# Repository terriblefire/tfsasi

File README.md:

# TFSASI - SASI to SCSI Adapter

A 3-way universal adapter board for connecting SASI 20-pin, SASI 26-pin, or SCSI 50-pin devices.

> **ℹ️ Tested:** SASI 20-pin (J1) with an X68000 EXPERT and a BlueSCSI.
>
> **⚠️ WARNING:** The SASI 26-pin connector (J2) has not yet been tested. Use at your own risk.

## Overview

This adapter allows you to connect:
- SASI 20-pin devices to SCSI 50-pin controllers
- SASI 26-pin devices to SCSI 50-pin controllers
- Mix and match between different SASI and SCSI interfaces

## Features

- **3-way adapter**: SASI 20-pin, SASI 26-pin, and SCSI 50-pin connectors
- **4-layer PCB design** for improved signal integrity
- **All signals properly mapped** between connectors
- **LED header connections provided** - Separate headers are included for HDD activity LED signals (SASI-20 pin 12, SASI-26 pin 16) to allow for custom LED driver circuits
- **Mirrored connector footprints** for proper cable orientation
- **Full SCSI-1 compatibility** with parity and attention signals (on 26-pin)

## Connectors

### SASI 20-Pin (J1)
- 2x10 pin header (0.1" pitch)
- Basic SASI interface with data and control signals
- No parity or attention signals
- Pin 12 (LED) is not connected

### SASI 26-Pin (J2)
- 2x13 pin header (0.1" pitch)
- Full SCSI-compatible with parity and attention
- Includes TERMPWR (+5V for termination)
- Pin 16 (LED) is not connected

### SCSI 50-Pin (J3)
- 2x25 pin header (0.1" pitch)
- Standard SCSI-1 interface
- Pin 18 (DBP/parity) connects from SASI 26-pin
- Pin 32 (ATN) connects from SASI 26-pin only

## Assembly

All three connector footprints are **mirrored** (a mirror image of a standard header when viewed from the top). The connectors must therefore be fitted on specific sides of the board, or the signals will be scrambled (odd/even rows swapped):

| Connector | Part | Fit on | Mates with |
|-----------|------|--------|------------|
| J1 (SASI 20-pin) | Male pin header | **Bottom** side (pins pointing down) | Ribbon cable, plugged in from below |
| J2 (SASI 26-pin) | Male pin header | **Bottom** side (pins pointing down) | Ribbon cable, plugged in from below |
| J3 (SCSI 50-pin) | Female pin socket | **Top** side | Male 50-pin header of the SCSI device (e.g. BlueSCSI), mounted face-to-face from above |

- Orient each ribbon cable so the stripe (pin 1) is at the square pad end.
- Leave JP1/JP2 open unless you need the LED signal; SCSI pin 34 is GND on most SCSI devices.
- **Verify after assembly:** with everything connected, check continuity from SASI pin 1 (-DB0) to SCSI pin 2 (-DB0). If SASI pin 1 instead connects to SCSI pin 4, the rows are swapped.

## Documentation

- [PINOUTS.md](PINOUTS.md) - Complete pinout documentation for all connectors
- [LED_SPECIFICATIONS.md](LED_SPECIFICATIONS.md) - Information about LED signal characteristics

## PCB Files

The Eagle schematic and board files are in the `eagle/` directory:
- `tfsasi.sch` - Complete schematic
- `tfsasi.brd` - PCB layout (to be created)

**Note:** The board is configured as a 4-layer PCB with one layer missing. This is intentional for the design requirements.

## Building Gerbers

### Using Make (with Docker)

```bash
cd eagle
make gerbers    # Generate Gerbers and create ZIP
make pdf        # Generate PDF schematic
make clean      # Clean generated files
```

Requires Docker with the `terriblefire78/eagle:v1` image.

### Automated Builds

GitHub Actions automatically generate:
- **Gerber files** on every push to main
- **PDF schematics** on every push to main
- **Release artifacts** when you create a version tag

## Manufacturing

The board is designed for JLCPCB 4-layer manufacturing:
- Standard 1.6mm thickness
- ENIG or HASL finish recommended
- 0.1" (2.54mm) through-hole connectors

## Signal Mapping

All data lines (DB0-DB7) and control signals (BSY, ACK, RST, MSG, SEL, C/D, REQ, I/O) are connected across all three connectors.

Special signals:
- **DBP (Parity)**: Only on SASI 26-pin and SCSI 50-pin
- **ATN (Attention)**: Only on SASI 26-pin and SCSI 50-pin
- **TERMPWR**: Only on SASI 26-pin and SCSI 50-pin
- **LED**: Separate headers provided for HDD activity LED signals from SASI-20 pin 12 and SASI-26 pin 16 (see [LED_SPECIFICATIONS.md](LED_SPECIFICATIONS.md) for driver circuit information)

## License

This project is licensed under the Creative Commons Attribution-ShareAlike 4.0 International License.

See [LICENSE](LICENSE) for details.

## Author

TerribleFire

## Contributing

Contributions are welcome! Please feel free to submit pull requests or open issues for bugs and feature requests.

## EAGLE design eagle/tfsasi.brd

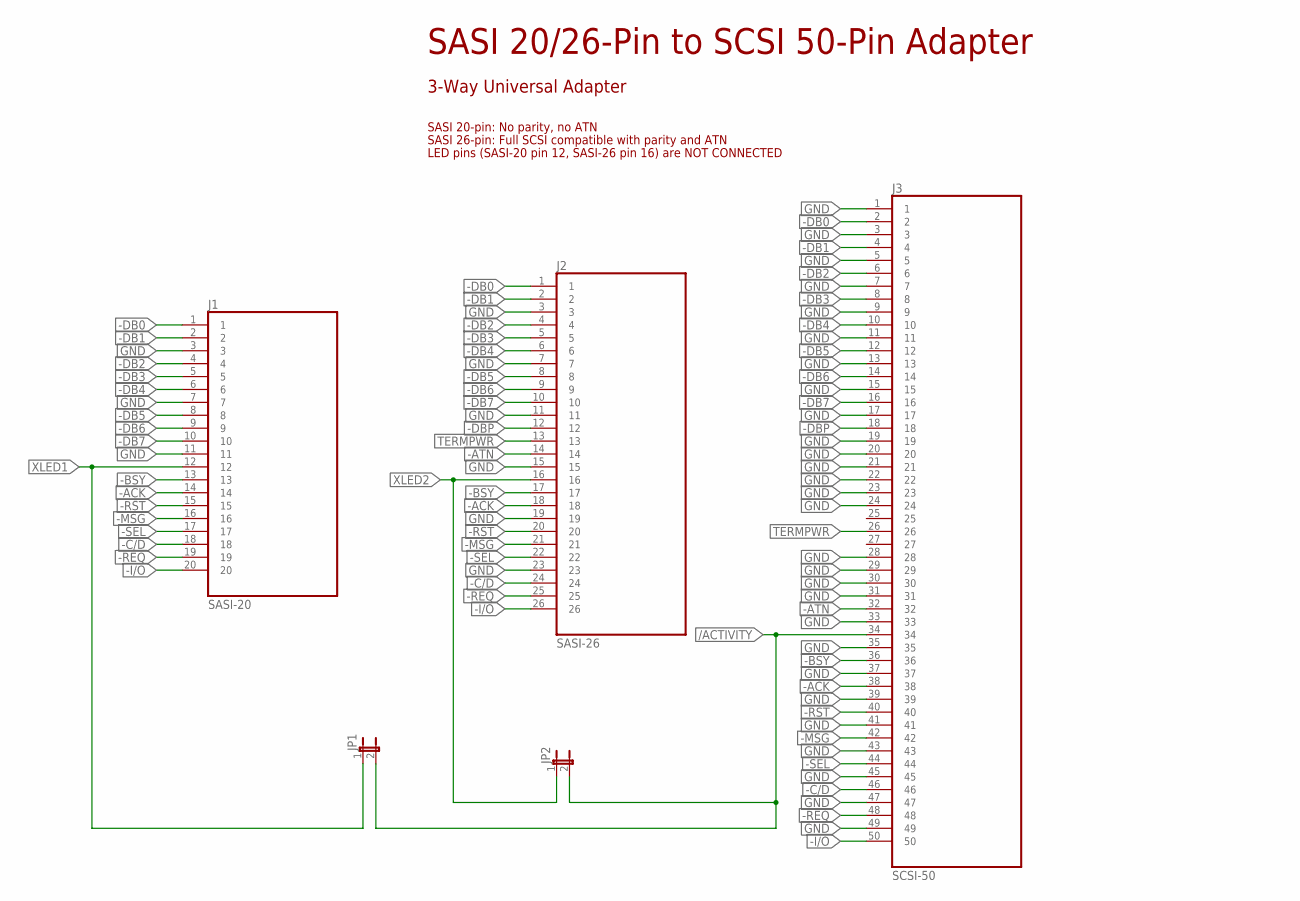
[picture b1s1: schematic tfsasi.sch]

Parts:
J1: SASI-20; 2X10
J2: SASI-26; 2X13
J3: SCSI-50; 2X25
JP1, JP2: JUMPER-2PTH; 1X02

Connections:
-ACK: J1.14, J2.18, J3.38
-ATN: J2.14, J3.32
-BSY: J1.13, J2.17, J3.36
-C/D: J1.18, J2.24, J3.46
-DB0: J1.1, J2.1, J3.2
-DB1: J1.2, J2.2, J3.4
-DB2: J1.4, J2.4, J3.6
-DB3: J1.5, J2.5, J3.8
-DB4: J1.6, J2.6, J3.10
-DB5: J1.8, J2.8, J3.12
-DB6: J1.9, J2.9, J3.14
-DB7: J1.10, J2.10, J3.16
-DBP: J2.12, J3.18
-I/O: J1.20, J2.26, J3.50
-MSG: J1.16, J2.21, J3.42
-REQ: J1.19, J2.25, J3.48
-RST: J1.15, J2.20, J3.40
-SEL: J1.17, J2.22, J3.44
/ACTIVITY: J3.34, JP1.2, JP2.2
GND: J1.3, J1.7, J1.11, J2.3, J2.7, J2.11, J2.15, J2.19, J2.23, J3.1, J3.3, J3.5, J3.7, J3.9, J3.11, J3.13, J3.15, J3.17, J3.19, J3.20, J3.21, J3.22, J3.23, J3.24, J3.28, J3.29, J3.30, J3.31, J3.33, J3.35, J3.37, J3.39, J3.41, J3.43, J3.45, J3.47, J3.49
TERMPWR: J2.13, J3.26
XLED1: J1.12, JP1.1
XLED2: J2.16, JP2.1

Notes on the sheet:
SASI 20/26-Pin to SCSI 50-Pin Adapter
3-Way Universal Adapter
SASI 20-pin: No parity, no ATN
SASI 26-pin: Full SCSI compatible with parity and ATN
LED pins (SASI-20 pin 12, SASI-26 pin 16) are NOT CONNECTED

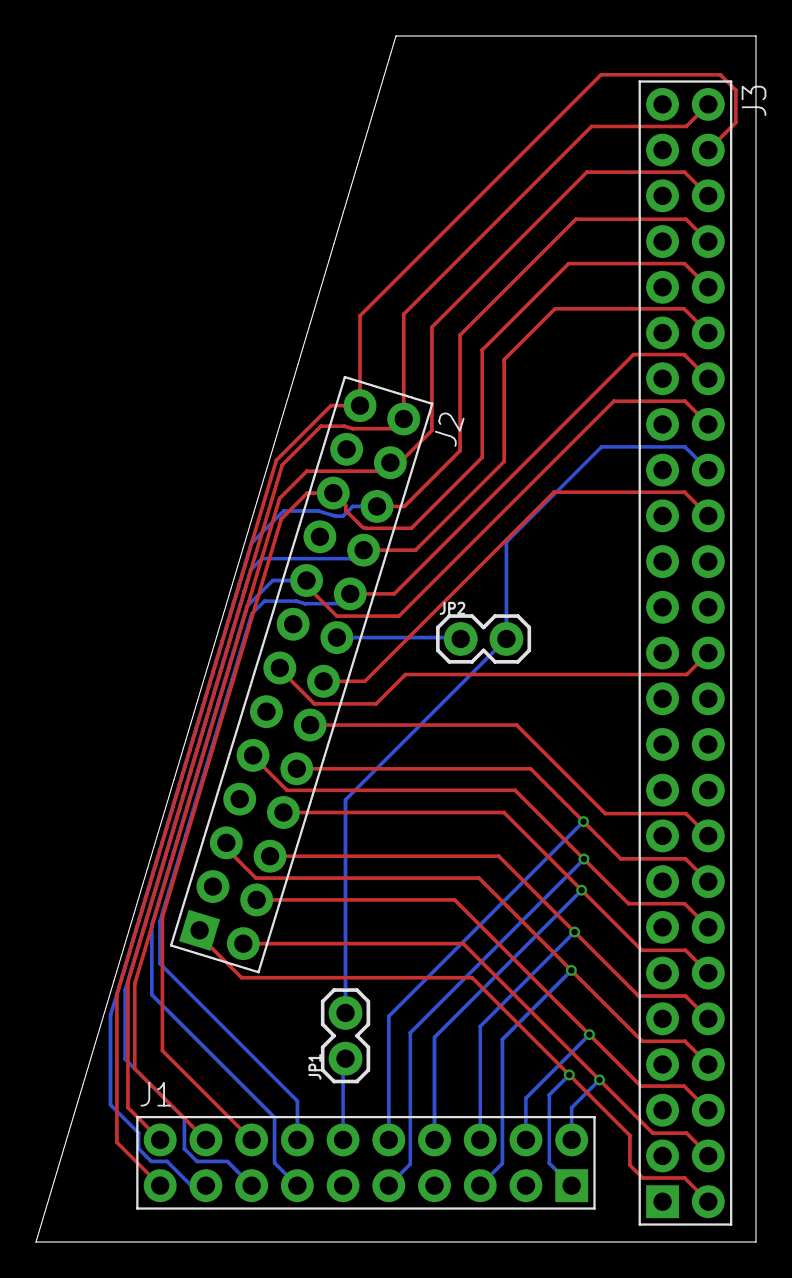
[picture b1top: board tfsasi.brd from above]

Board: 4 copper layers, 40.0 x 67.0 mm, 5 parts (0 on the bottom side), 23 nets.

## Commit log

2025-11-12 Initial commit: SASI 20/26-pin to SCSI 50-pin adapter
    - Complete Eagle schematic with mirrored connectors
    - 3-way adapter: SASI 20-pin, SASI 26-pin, and SCSI 50-pin
    - Pinout documentation for all connectors
    - LED signal specifications
    - GitHub workflows for automated Gerber and PDF generation
    - Makefile for local Gerber generation using Docker
2025-11-12 Remove .claude folder from version control and add to .gitignore
2025-11-12 Add comprehensive README documentation
2025-11-12 Add GitHub Actions build status badges to README
2025-11-12 Add board image to README
2025-11-12 Add note about 4-layer board configuration with one layer missing
2025-11-12 Fix PDF generation: explicitly call Python script in Docker container
2025-11-12 Add warning that board has not yet been tested
2025-11-12 Clarify that LED headers are provided for custom LED driver circuits
2025-11-17 Fixed thermal widths

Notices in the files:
parts and their libraries:
SparkFun-Retired: Licensing: Creative Commons ShareAlike 4.0 International - https://creativecommons.org/licenses/by-sa/4.0
